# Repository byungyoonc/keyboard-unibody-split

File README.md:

# keyboard-unibody-split
Unibody split keyboard

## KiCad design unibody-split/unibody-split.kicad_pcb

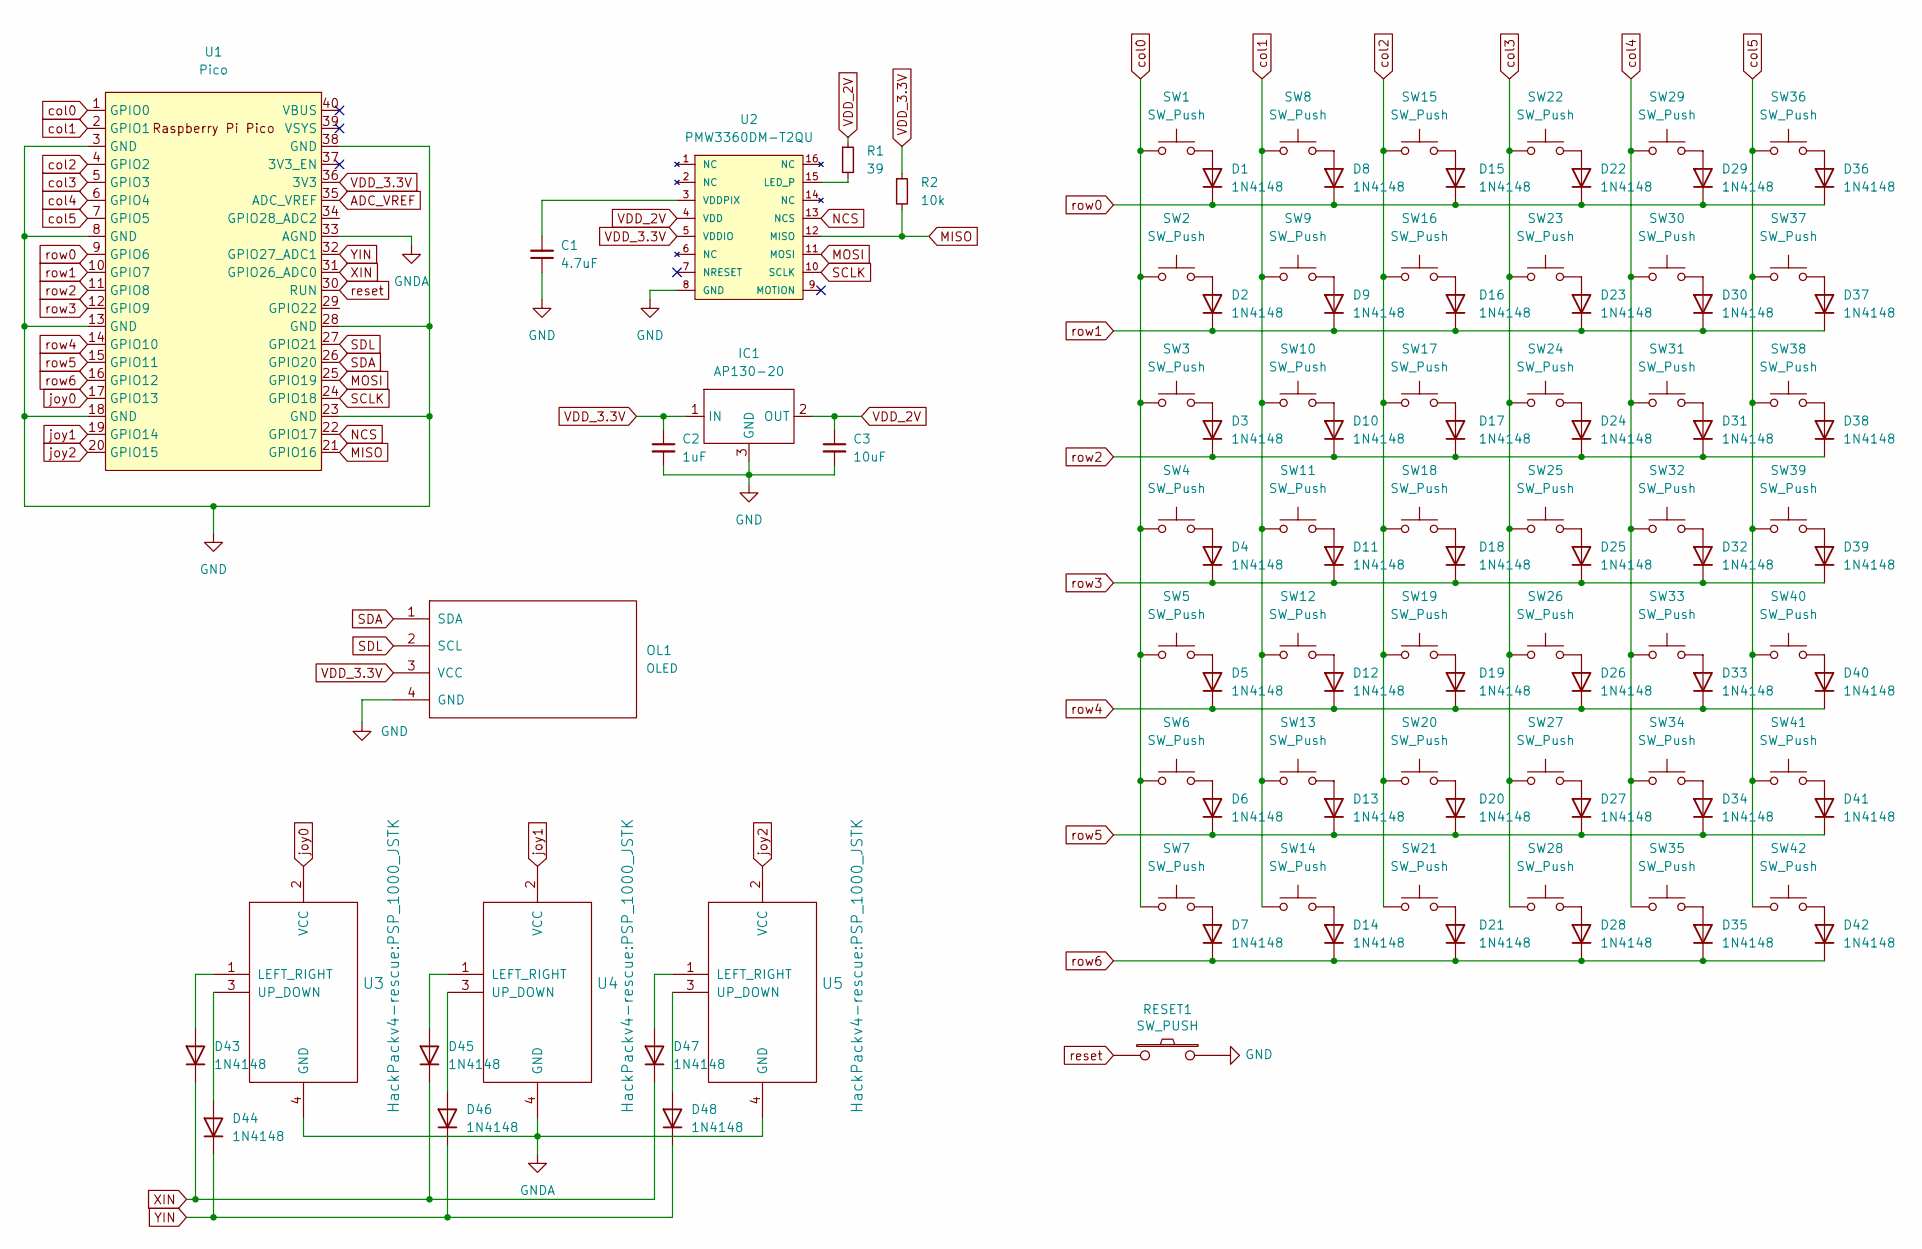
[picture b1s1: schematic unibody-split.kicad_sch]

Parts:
C1: 4.7uF; C_0805_2012Metric
C2: 1uF; C_0805_2012Metric
C3: 10uF; C_0805_2012Metric
D1, D2, D3, D4, D5, D6, D7, D8, D9, D10, D11, D12, D13, D14, D15, D16, D17, D18, D19, D20, D21, D22, D23, D24, D25, D26, D27, D28, D29, D30, D31, D32, D33, D34, D35, D36, D37, D38, D39, D40, D41, D42, D43, D44, D45, D46, D47, D48: 1N4148; D_DO-35_SOD27_P7.62mm_Horizontal
IC1: AP130-20; SOT-23
OL1: OLED; OLED_v2
R1: 39; R_0805_2012Metric
R2: 10k; R_0805_2012Metric
RESET1: SW_PUSH; SW_SPST_B3U-1000P
SW1, SW2, SW3, SW4, SW5, SW6, SW7, SW8, SW9, SW10, SW11, SW12, SW13, SW14, SW15, SW16, SW17, SW18, SW19, SW20, SW21, SW22, SW23, SW24, SW25, SW26, SW27, SW28, SW29, SW30, SW31, SW32, SW33, SW34, SW35, SW36, SW37, SW38, SW39, SW40, SW41, SW42: SW_Push; MX_Choc_Hotswap
U1: Pico; RPi_Pico_SMD_TH
U2: PMW3360DM-T2QU; DIP-16_W10.16mm
U3, U4, U5: HackPackv4-rescue:PSP_1000_JSTK; JOYSTICK-PSP1000

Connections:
ADC_VREF: U1.35 (ADC_VREF)
GND: C1.1, C2.2, C3.2, IC1.3 (GND), OL1.4 (GND), RESET1.2, U1.3 (GND), U1.8 (GND), U1.13 (GND), U1.18 (GND), U1.23 (GND), U1.28 (GND), U1.38 (GND), U2.8 (GND)
MISO: R2.2, U1.21 (GPIO16), U2.12 (MISO)
MOSI: U1.25 (GPIO19), U2.11 (MOSI)
NCS: U1.22 (GPIO17), U2.13 (NCS)
unnamed: C1.2, U2.3 (VDDPIX)
unnamed: D1.2 (A), SW1.2
unnamed: D2.2 (A), SW2.2
unnamed: D3.2 (A), SW3.2
unnamed: D4.2 (A), SW4.2
unnamed: D5.2 (A), SW5.2
unnamed: D6.2 (A), SW6.2
unnamed: D7.2 (A), SW7.2
unnamed: D8.2 (A), SW8.2
unnamed: D9.2 (A), SW9.2
unnamed: D10.2 (A), SW10.2
unnamed: D11.2 (A), SW11.2
unnamed: D12.2 (A), SW12.2
unnamed: D13.2 (A), SW13.2
unnamed: D14.2 (A), SW14.2
unnamed: D15.2 (A), SW15.2
unnamed: D16.2 (A), SW16.2
unnamed: D17.2 (A), SW17.2
unnamed: D18.2 (A), SW18.2
unnamed: D19.2 (A), SW19.2
unnamed: D20.2 (A), SW20.2
unnamed: D21.2 (A), SW21.2
unnamed: D22.2 (A), SW22.2
unnamed: D23.2 (A), SW23.2
unnamed: D24.2 (A), SW24.2
unnamed: D25.2 (A), SW25.2
unnamed: D26.2 (A), SW26.2
unnamed: D27.2 (A), SW27.2
unnamed: D28.2 (A), SW28.2
unnamed: D29.2 (A), SW29.2
unnamed: D30.2 (A), SW30.2
unnamed: D31.2 (A), SW31.2
unnamed: D32.2 (A), SW32.2
unnamed: D33.2 (A), SW33.2
unnamed: D34.2 (A), SW34.2
unnamed: D35.2 (A), SW35.2
unnamed: D36.2 (A), SW36.2
unnamed: D37.2 (A), SW37.2
unnamed: D38.2 (A), SW38.2
unnamed: D39.2 (A), SW39.2
unnamed: D40.2 (A), SW40.2
unnamed: D41.2 (A), SW41.2
unnamed: D42.2 (A), SW42.2
unnamed: D43.2 (A), U3.1 (LEFT_RIGHT)
unnamed: D44.2 (A), U3.3 (UP_DOWN)
unnamed: D45.2 (A), U4.1 (LEFT_RIGHT)
unnamed: D46.2 (A), U4.3 (UP_DOWN)
unnamed: D47.2 (A), U5.1 (LEFT_RIGHT)
unnamed: D48.2 (A), U5.3 (UP_DOWN)
unnamed: R1.2, U2.15 (LED_P)
SCLK: U1.24 (GPIO18), U2.10 (SCLK)
SDA: OL1.1 (SDA), U1.26 (GPIO20)
SDL: OL1.2 (SCL), U1.27 (GPIO21)
VDD_2V: C3.1, IC1.2 (OUT), R1.1, U2.4 (VDD)
VDD_3.3V: C2.1, IC1.1 (IN), OL1.3 (VCC), R2.1, U1.36 (3V3), U2.5 (VDDIO)
XIN: D43.1 (K), D45.1 (K), D47.1 (K), U1.31 (GPIO26_ADC0)
YIN: D44.1 (K), D46.1 (K), D48.1 (K), U1.32 (GPIO27_ADC1)
col0: SW1.1, SW2.1, SW3.1, SW4.1, SW5.1, SW6.1, SW7.1, U1.1 (GPIO0)
col1: SW8.1, SW9.1, SW10.1, SW11.1, SW12.1, SW13.1, SW14.1, U1.2 (GPIO1)
col2: SW15.1, SW16.1, SW17.1, SW18.1, SW19.1, SW20.1, SW21.1, U1.4 (GPIO2)
col3: SW22.1, SW23.1, SW24.1, SW25.1, SW26.1, SW27.1, SW28.1, U1.5 (GPIO3)
col4: SW29.1, SW30.1, SW31.1, SW32.1, SW33.1, SW34.1, SW35.1, U1.6 (GPIO4)
col5: SW36.1, SW37.1, SW38.1, SW39.1, SW40.1, SW41.1, SW42.1, U1.7 (GPIO5)
joy0: U1.17 (GPIO13), U3.2 (VCC)
joy1: U1.19 (GPIO14), U4.2 (VCC)
joy2: U1.20 (GPIO15), U5.2 (VCC)
reset: RESET1.1, U1.30 (RUN)
row0: D1.1 (K), D8.1 (K), D15.1 (K), D22.1 (K), D29.1 (K), D36.1 (K), U1.9 (GPIO6)
row1: D2.1 (K), D9.1 (K), D16.1 (K), D23.1 (K), D30.1 (K), D37.1 (K), U1.10 (GPIO7)
row2: D3.1 (K), D10.1 (K), D17.1 (K), D24.1 (K), D31.1 (K), D38.1 (K), U1.11 (GPIO8)
row3: D4.1 (K), D11.1 (K), D18.1 (K), D25.1 (K), D32.1 (K), D39.1 (K), U1.12 (GPIO9)
row4: D5.1 (K), D12.1 (K), D19.1 (K), D26.1 (K), D33.1 (K), D40.1 (K), U1.14 (GPIO10)
row5: D6.1 (K), D13.1 (K), D20.1 (K), D27.1 (K), D34.1 (K), D41.1 (K), U1.15 (GPIO11)
row6: D7.1 (K), D14.1 (K), D21.1 (K), D28.1 (K), D35.1 (K), D42.1 (K), U1.16 (GPIO12)

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
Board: 2 copper layers, 103 parts (57 on the bottom side), 79 nets, no tracks yet.

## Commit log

2022-07-02 Init KiCad project
2022-08-10 Add submodules
2022-08-10 Modified symbol/footprint library table
2022-08-14 Add submodule for trackball sensor
2022-08-14 Add/Modify fp/sym
2022-08-14 Modified schema: 42 keys and trackball sensor setup
2022-08-15 Add submodule/fp/sym for joystick
2022-08-15 Add joystick to schematics
2022-08-15 Add submodule/fp/sym for OLED
2022-08-15 Add OLED to schematics
2022-08-15 Update PCB from schema, layout formed
2022-08-15 disconnected bottom GND in RPi-Pico
2022-08-15 Update PCB by adding edge cuts
2022-08-16 Changed thumb clusters rotation
2022-08-19 Added two more analog sticks
2022-08-19 Removed RPi-Pico debug pins, Updated PCB to contain 3 joysticks
2022-08-21 Done routing PCB
2022-08-22 Updated PCB routing, added thread holes
2022-08-23 Add trackball holder screw hole
2022-08-23 Align things for top plate design
2022-08-23 Further alignment
2022-08-24 Top plate under construction
